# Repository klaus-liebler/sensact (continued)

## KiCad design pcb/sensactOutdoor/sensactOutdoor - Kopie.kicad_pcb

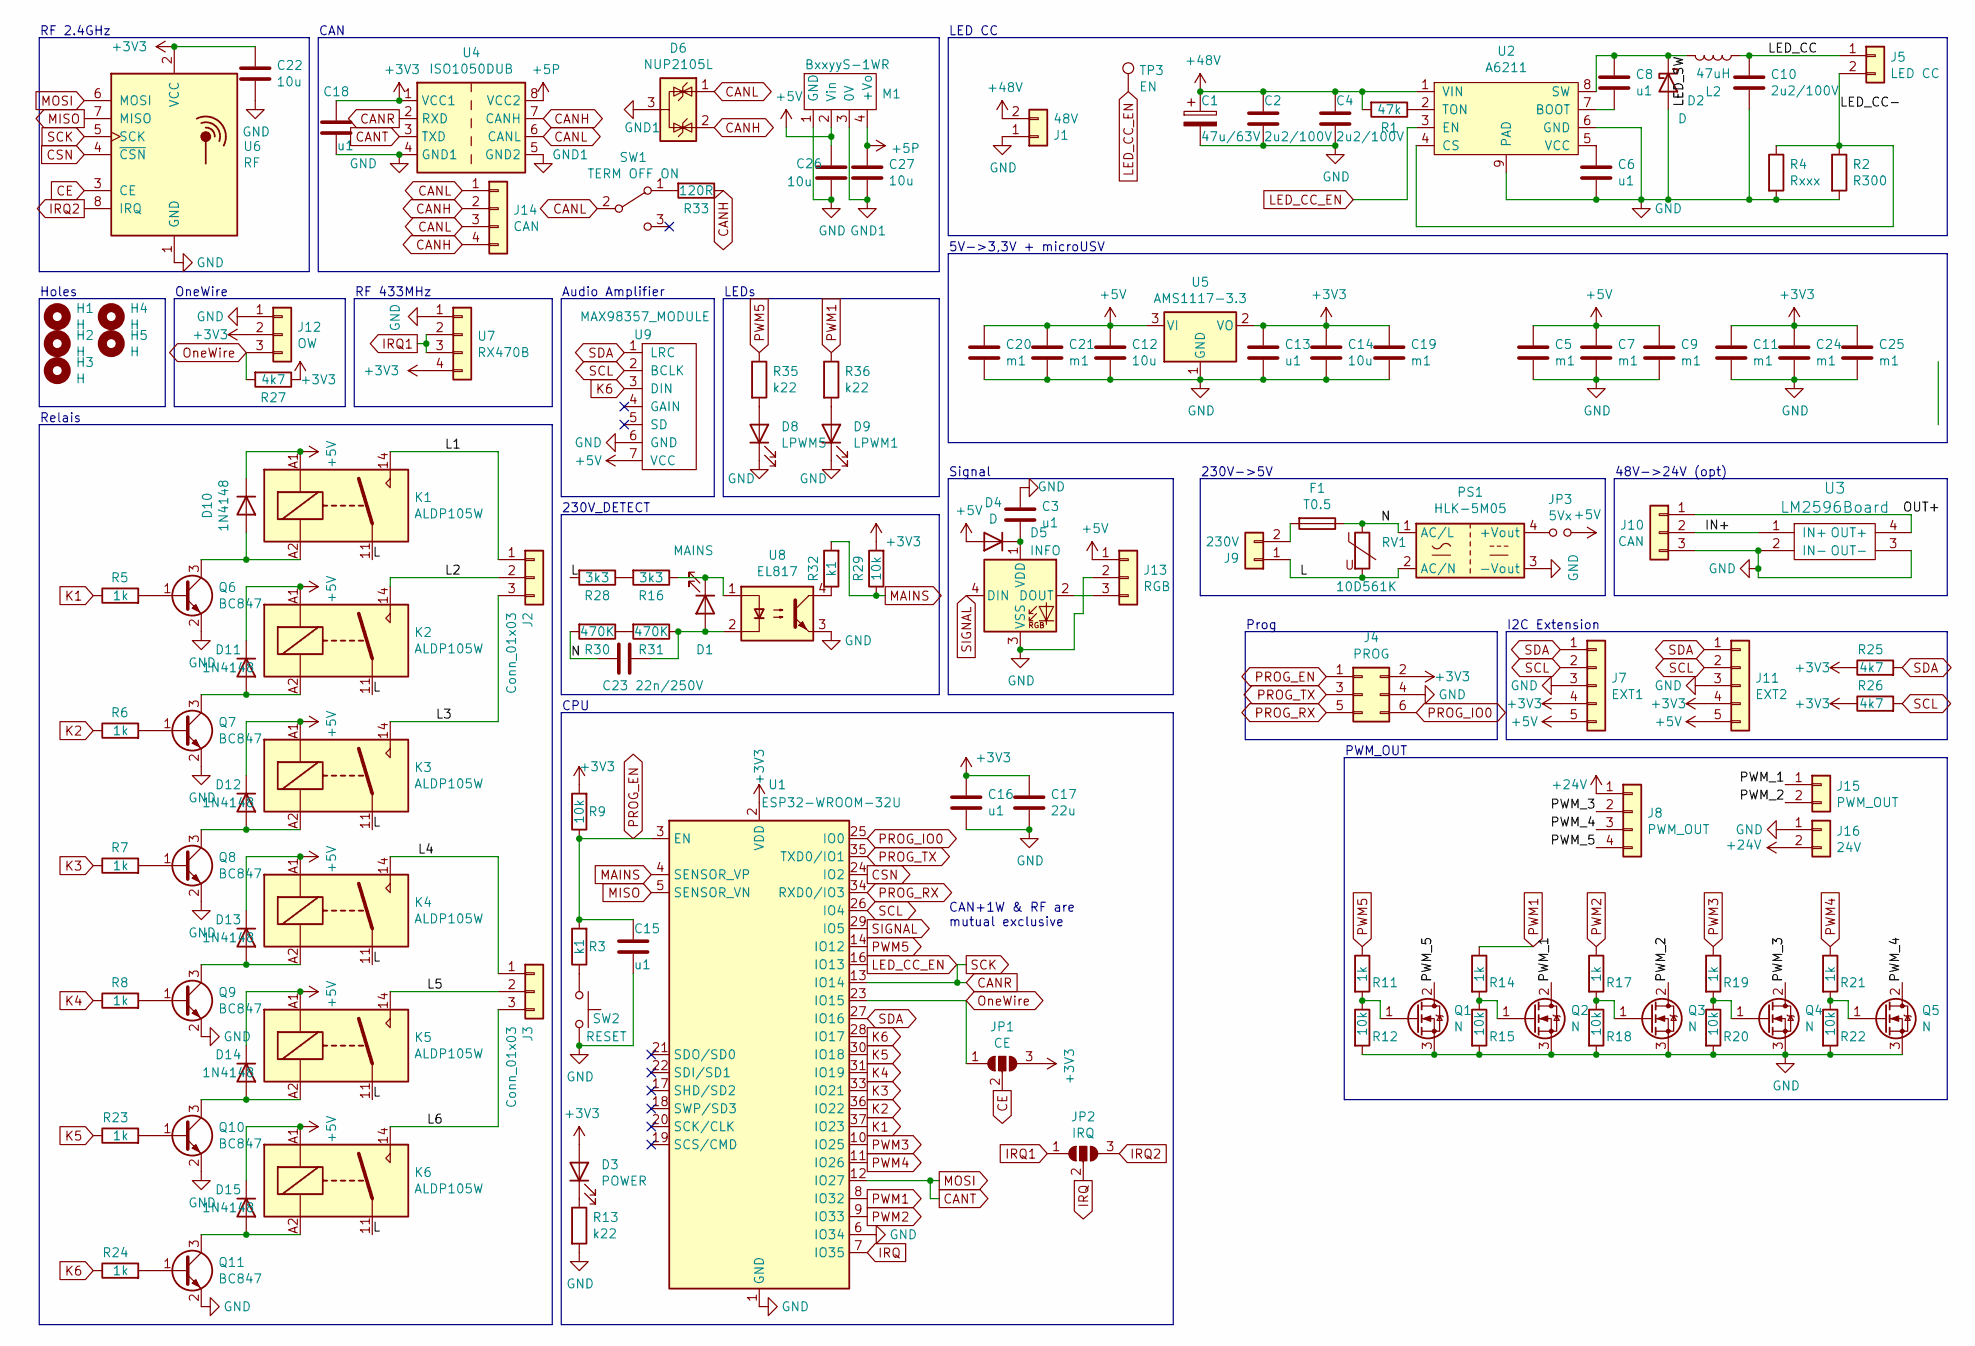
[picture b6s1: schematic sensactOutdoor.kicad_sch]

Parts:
C1: 47u/63V; CP_Radial_D8.0mm_P3.50mm
C2, C4, C10: 2u2/100V; C_1206_3216Metric_Pad1.33x1.80mm_HandSolder
C3, C6, C8, C13, C15, C16, C18: u1; C_0805_2012Metric_Pad1.18x1.45mm_HandSolder
C5, C7, C9, C11, C19, C20, C21, C24, C25: m1; C_1206_3216Metric_Pad1.33x1.80mm_HandSolder
C12, C14, C22, C26, C27: 10u; C_1206_3216Metric_Pad1.33x1.80mm_HandSolder
C17: 22u; C_1206_3216Metric_Pad1.33x1.80mm_HandSolder
C23: 22n/250V; C_Rect_L11.0mm_W5.1mm_P10.00mm_MKT
D1: MAINS; LED_0805_2012Metric_Pad1.15x1.40mm_HandSolder
D2, D4: D; D_SMA_Handsoldering
D3: POWER; LED_D5.0mm
D5: INFO; WS2812b_handsolder
D6: NUP2105L; SOT-23_Handsoldering
D8: LPWM5; LED_0805_2012Metric_Pad1.15x1.40mm_HandSolder
D9: LPWM1; LED_0805_2012Metric_Pad1.15x1.40mm_HandSolder
D10, D11, D12, D13, D14, D15: 1N4148; D_SOD-123_handsolder
F1: T0.5; Fuse_Littelfuse_372_D8.50mm
H1, H2, H3, H4, H5: H; MountingHole_3.2mm_M3
J1: 48V; PhoenixContact_MSTBV_2,5_2-G-5,08_1x02_P5.08mm_Vertical
J2, J3: Conn_01x03; PhoenixContact_GMSTBVA_2,5_3-G-7,62_1x03_P7.62mm_Vertical
J4: PROG; IDC_2x03_P1.27mm_Vertical
J5: LED CC; PhoenixContact_MSTBV_2,5_2-G-5,08_1x02_P5.08mm_Vertical
J7: EXT1; JST_XH_B5B-XH-A_1x05_P2.50mm_Vertical
J8: PWM_OUT; PhoenixContact_MCV_1,5_4-G-3.5_1x04_P3.50mm_Vertical
J9: 230V; PhoenixContact_GMSTBVA_2,5_2-G-7,62_1x02_P7.62mm_Vertical
J10: CAN; KF250-3.5-3P-A
J11: EXT2; JST_XH_B5B-XH-A_1x05_P2.50mm_Vertical
J12: OW; KF250-3.5-3P-A
J13: RGB; KF250-3.5-3P-A
J14: CAN; PhoenixContact_MCV_1,5_4-G-3.5_1x04_P3.50mm_Vertical
J15: PWM_OUT; PhoenixContact_MCV_1,5_2-G-3.5_1x02_P3.50mm_Vertical
J16: 24V; PhoenixContact_MSTBV_2,5_2-G-5,08_1x02_P5.08mm_Vertical
JP1: CE; SolderJumper-3_P1.3mm_Open_RoundedPad1.0x1.5mm_NumberLabels
JP2: IRQ; SolderJumper-3_P1.3mm_Open_RoundedPad1.0x1.5mm_NumberLabels
JP3: 5Vx; PinHeader_1x02_P2.54mm_Vertical
K1, K2, K3, K4, K5, K6: ALDP105W; RELAY_ALDP105W
L2: 47uH; L_1040
M1: BxxyyS-1WR; BxxxxS-1W
PS1: HLK-5M05; CONV_HLK-5M05
Q1, Q2, Q3, Q4, Q5: N; TO-220F-3_Vertical
Q6, Q7, Q8, Q9, Q10, Q11: BC847; SOT-23_Handsoldering
R1: 47k; R_0805_2012Metric_Pad1.20x1.40mm_HandSolder
R2: R300; R_1206_3216Metric_Pad1.30x1.75mm_HandSolder
R3, R32: k1; R_0805_2012Metric_Pad1.20x1.40mm_HandSolder
R4: Rxxx; R_2512_6332Metric_Pad1.40x3.35mm_HandSolder
R5, R6, R7, R8, R11, R14, R17, R19, R21, R23, R24: 1k; R_0805_2012Metric_Pad1.20x1.40mm_HandSolder
R9, R12, R15, R18, R20, R22, R29: 10k; R_0805_2012Metric_Pad1.20x1.40mm_HandSolder
R13, R35, R36: k22; R_0805_2012Metric_Pad1.20x1.40mm_HandSolder
R16, R28: 3k3; R_2512_6332Metric_Pad1.40x3.35mm_HandSolder
R25, R26, R27: 4k7; R_0805_2012Metric_Pad1.20x1.40mm_HandSolder
R30, R31: 470K; R_2512_6332Metric_Pad1.40x3.35mm_HandSolder
R33: 120R; R_1206_3216Metric_Pad1.30x1.75mm_HandSolder
RV1: 10D561K; RV_Disc_D12mm_W3.9mm_P7.5mm
SW1: TERM OFF ON; SS12D00
SW2: RESET; SW_Push_1P1T_NO_6x6mm_H9.5mm
TP3: EN; TestPoint_THTPad_D2.0mm_Drill1.0mm
U1: ESP32-WROOM-32U; ESP32-WROOM-32_HANDSOLDER
U2: A6211; SOIC-8_3.9x4.9mm_Pitch1.27mm_pad_handsolder
U3: LM2596Board; LM2596HV
U4: ISO1050DUB; SOP-8_6.62x9.15mm_P2.54mm_handsolder
U5: AMS1117-3.3; SOT-223-3_TabPin2_HANDSOLDER
U6: RF; nRF24L01_Breakout
U7: RX470B; PinHeader_1x04_P2.54mm_Vertical
U8: EL817; SO-4_7.6x3.6mm_P2.54mm_handsolder
U9: MAX98357_MODULE; PinHeader_1x07_P2.54mm_Vertical

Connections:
+5P: C27.1, M1.4 (+Vo), U4.8 (VCC2)
+5V: C5.1, C7.1, C9.1, C12.1, C20.1, C21.1, C26.1, D4.2 (A), D10.1 (K), D11.1 (K), D12.1 (K), D13.1 (K), D14.1 (K), D15.1 (K), J7.5, J11.5, J13.1, JP3.2, K1.A1, K2.A1, K3.A1, K4.A1, K5.A1, K6.A1, M1.2 (Vin), U5.3 (VI), U9.7 (VCC)
+24V: J8.1, J16.2
+48V: C1.1, C2.1, C4.1, J1.2, R1.2, U2.1 (VIN)
/IN+: J10.2, U3.1 (IN+)
/L: J9.1, K1.11, K2.11, K3.11, K4.11, K5.11, K6.11, PS1.2 (AC/N), R28.2, RV1.2
/L1: J2.1, K1.14
/L2: J2.2, K2.14
/L3: J2.3, K3.14
/L4: J3.1, K4.14
/L5: J3.2, K5.14
/L6: J3.3, K6.14
/LED_CC: C10.1, J5.1, L2.1
/LED_CC-: J5.2, R2.1, R4.1, U2.4 (CS)
/LED_SW: C8.1, D2.1 (K), L2.2, U2.8 (SW)
/N: C23.1, F1.1, PS1.1 (AC/L), R30.2, RV1.1
/OUT+: J10.1, U3.4 (OUT+)
/PWM_1: J15.1, Q2.2 (D)
/PWM_2: J15.2, Q3.2 (D)
/PWM_3: J8.2, Q4.2 (D)
/PWM_4: J8.3, Q5.2 (D)
/PWM_5: J8.4, Q1.2 (D)
CANH: D6.2 (K), J14.2, J14.4, R33.1, U4.7 (CANH)
CANL: D6.1 (K), J14.1, J14.3, SW1.2 (B), U4.6 (CANL)
CANR: U1.13 (IO14), U4.2 (RXD), U6.5 (SCK)
CANT: U1.12 (IO27), U4.3 (TXD), U6.6 (MOSI)
CE: JP1.2 (C), U6.3 (CE)
CSN: U1.24 (IO2), U6.4 (~CSN)
GND1: C27.2, D6.3 (A), M1.3 (0V), U4.5 (GND2)
IRQ: JP2.2 (C), U1.7 (IO35)
IRQ1: JP2.1 (A), U7.2, U7.3
IRQ2: JP2.3 (B), U6.8 (IRQ)
K1: R5.1, U1.37 (IO23)
K2: R6.1, U1.36 (IO22)
K3: R7.1, U1.33 (IO21)
K4: R8.1, U1.31 (IO19)
K5: R23.1, U1.30 (IO18)
K6: R24.1, U1.28 (IO17), U9.3 (DIN)
LED_CC_EN: TP3.1, U1.16 (IO13), U2.3 (EN)
MAINS: R29.1, R32.2, U1.4 (SENSOR_VP)
MISO: U1.5 (SENSOR_VN), U6.7 (MISO)
unnamed: C3.2, D4.1 (K), D5.1 (VDD)
unnamed: C6.1, U2.5 (VCC)
unnamed: C8.2, U2.7 (BOOT)
unnamed: C23.2, D1.2 (A), R31.1, U8.2
unnamed: D1.1 (K), R16.1, U8.1
unnamed: D3.1 (K), R13.1
unnamed: D5.2 (DOUT), J13.3
unnamed: D8.2 (A), R35.2
unnamed: D9.2 (A), R36.2
unnamed: D10.2 (A), K1.A2, Q6.3 (C)
unnamed: D11.2 (A), K2.A2, Q7.3 (C)
unnamed: D12.2 (A), K3.A2, Q8.3 (C)
unnamed: D13.2 (A), K4.A2, Q9.3 (C)
unnamed: D14.2 (A), K5.A2, Q10.3 (C)
unnamed: D15.2 (A), K6.A2, Q11.3 (C)
unnamed: F1.2, J9.2
unnamed: JP3.1, PS1.4 (+Vout)
unnamed: Q1.1 (G), R11.2, R12.1
unnamed: Q2.1 (G), R14.2, R15.1
unnamed: Q3.1 (G), R17.2, R18.1
unnamed: Q4.1 (G), R19.2, R20.1
unnamed: Q5.1 (G), R21.2, R22.1
unnamed: Q6.1 (B), R5.2
unnamed: Q7.1 (B), R6.2
unnamed: Q8.1 (B), R7.2
unnamed: Q9.1 (B), R8.2
unnamed: Q10.1 (B), R23.2
unnamed: Q11.1 (B), R24.2
unnamed: R1.1, U2.2 (TON)
unnamed: R3.1, SW2.1
unnamed: R16.2, R28.1
unnamed: R30.1, R31.2
unnamed: R32.1, U8.4
unnamed: R33.2, SW1.1 (A)
OneWire: J12.3, JP1.1 (A), R27.2, U1.23 (IO15)
PROG_IO0: J4.6, U1.25 (IO0)
PROG_RX: J4.5, U1.34 (RXD0/IO3)
PROG_TX: J4.3, U1.35 (TXD0/IO1)
PWM1: R14.1, R36.1, U1.8 (IO32)
PWM2: R17.1, U1.9 (IO33)
PWM3: R19.1, U1.10 (IO25)
PWM4: R21.1, U1.11 (IO26)
PWM5: R11.1, R35.1, U1.14 (IO12)
SCL: J7.2, J11.2, R26.2, U1.26 (IO4), U9.2 (BCLK)
SDA: J7.1, J11.1, R25.2, U1.27 (IO16), U9.1 (LRC)
SIGNAL: D5.4 (DIN), U1.29 (IO5)

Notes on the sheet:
RF 433MHz
Relais
230V_DETECT
Holes
I2C Extension
CAN+1W & RF are mutual exclusive
PWM_OUT
CAN
Signal
LED CC
48V->24V (opt)
5V->3,3V + microUSV
RF 2.4GHz
CPU
OneWire
LEDs
230V->5V
Audio Amplifier
Prog

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
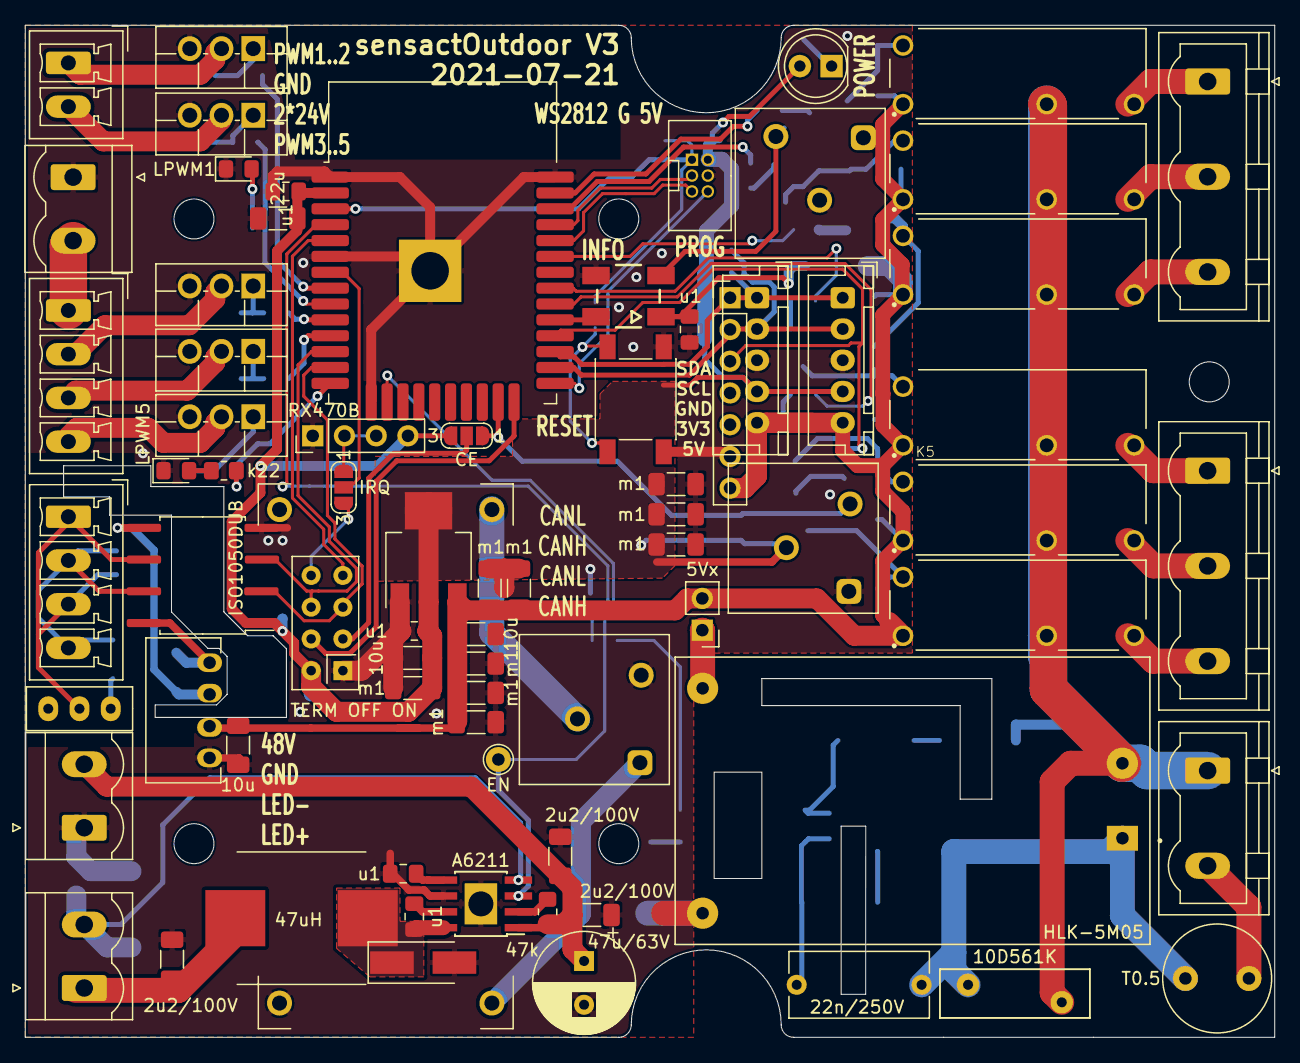
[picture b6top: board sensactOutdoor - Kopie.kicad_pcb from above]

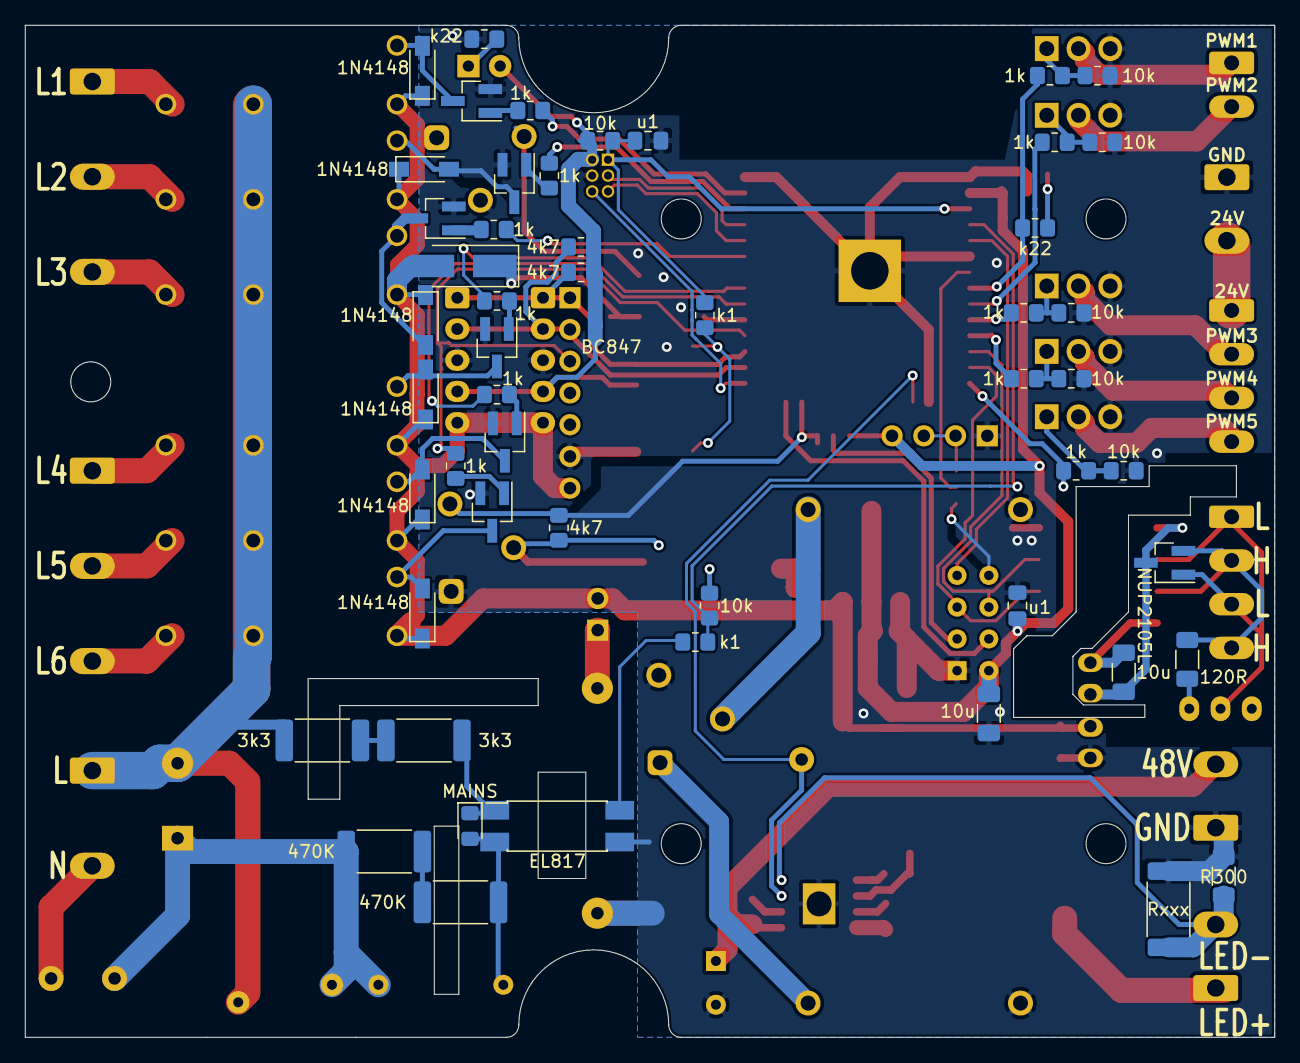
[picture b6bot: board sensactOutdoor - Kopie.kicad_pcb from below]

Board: 2 copper layers, 100.0 x 81.0 mm, 132 parts (52 on the bottom side), 90 nets.
